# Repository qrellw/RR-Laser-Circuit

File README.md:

# Tài liệu Kỹ thuật Dự án: Thiết bị Đo nhịp thở (RR-Laser-Circuit)

Tài liệu này cung cấp các thông số kỹ thuật, nguyên lý hoạt động và hướng dẫn cấu hình phần mềm cho hệ thống thiết bị đo nhịp thở ứng dụng cảm biến quang học.

## 1. Tổng quan Nguyên lý Hoạt động
Hệ thống đo nhịp thở dựa trên phương pháp đo chuyển vị quang học (Optical Displacement Sensing):
*   **Khối Phát:** Module Laser bán dẫn (bước sóng 650nm) chiếu tia sáng vào một gương phản xạ gắn trên lồng ngực.
*   **Khối Thu:** Hai photodiode (BPW34) được bố trí thành dạng bi-cell. Sự dịch chuyển của gương theo nhịp thở làm thay đổi vị trí tia phản xạ trên bề mặt bi-cell, dẫn đến sự thay đổi tương quan dòng quang điện giữa hai kênh.
*   **Khối Xử lý Tín hiệu (Analog):** Sử dụng duy nhất 1 Op-amp **MCP6004** (4 kênh). Hai kênh được cấu hình làm mạch Transimpedance Amplifier (TIA) để chuyển đổi dòng quang điện (µA) thành điện áp (Va, Vb). Hai kênh còn lại làm mạch Buffer để ổn định trở kháng trước khi đưa vào ADC.
*   **Khối Số hóa (Digital):** Vi điều khiển ESP32-C3 thu thập dữ liệu từ ADC (ADS1115) qua giao tiếp I2C, xử lý thuật toán và truyền dữ liệu qua giao thức Bluetooth Low Energy (BLE).

## 2. Sơ đồ Chân Vi điều khiển (Pinout)
*Thiết bị sử dụng module ESP32-C3 SuperMini.*

| Chức năng | Chân GPIO | Trạng thái Logic | Ghi chú |
| :--- | :--- | :--- | :--- |
| **I2C SDA** | GPIO8 | Bidirectional | Giao tiếp dữ liệu với ADS1115 |
| **I2C SCL** | GPIO9 | Output | Xung nhịp I2C cho ADS1115 |
| **LASER_EN** | GPIO4 | Output | HIGH: Bật công tắc MOSFET cấp dòng cho Laser (3.3V) |
| **VBAT_SENSE** | GPIO0 | Analog Input | Đọc điện áp Pin qua cầu phân áp 100k/100k (ADC1) |

*(Lưu ý: Thiết kế V1 đã loại bỏ hoàn toàn mạch Boost 5V. Laser được cấp trực tiếp nguồn 3.3V từ LDO. Chân `BOOST_EN` cũ đã bị xóa khỏi phần mềm).*

## 3. Cấu hình ADC (ADS1115) và Quy trình Lấy mẫu
*   **Địa chỉ I2C:** `0x48` (Chân ADDR nối GND).
*   **Độ phân giải:** 16-bit.
*   **Phân bổ Kênh (Multiplexer):**
    *   `AIN0` = Điện áp **Va** (Tín hiệu TIA kênh 1).
    *   `AIN1` = Điện áp **Vb** (Tín hiệu TIA kênh 2).
    *   `AIN2` = Điện áp **Vbias** (Mức nền tham chiếu thực tế, thường ~0.23V).

**Quy trình lấy mẫu (Sampling Sequence):**
Để triệt tiêu nhiễu môi trường và ánh sáng phòng, phần mềm cần thực hiện chu kỳ lấy mẫu theo trình tự nghiêm ngặt sau:
1.  Đặt `LASER_EN` = HIGH (Laser phát sáng).
2.  Trễ (Delay) **50ms** để mạch lọc RC (fc ≈ 15Hz) xác lập giá trị.
3.  Đọc giá trị ADC tại `AIN0`, `AIN1` và `AIN2` (Lưu vào biến `Va_on`, `Vb_on`, `Vbias`).
4.  Đặt `LASER_EN` = LOW (Tắt Laser).
5.  Trễ **50ms**.
6.  Đọc giá trị ADC tại `AIN0`, `AIN1` (Lưu vào biến `Va_off`, `Vb_off`).

## 4. Công thức Tính toán Tín hiệu
Mức nền thực tế (Vbias) được đọc từ `AIN2` giúp bù trừ sai số do nhiệt độ và dung sai linh kiện. Phần mềm cần thực hiện các bước tính toán sau:

1.  **Trích xuất dòng quang điện (tỉ lệ với điện áp):**
    *   `Ia = Va_on - Va_off`
    *   `Ib = Vb_on - Vb_off`
    *(Việc trừ mẫu sáng cho mẫu tối giúp triệt tiêu hoàn toàn mức nền Vbias và ánh sáng môi trường).*

2.  **Tính tỉ số vị trí (Position Ratio - r):**
    \[
 r = \frac{I_a - k \cdot I_b}{I_a + k \cdot I_b} 
\]
    *Trong đó:* `k` là hệ số bù sai lệch giữa hai kênh (được xác định thực nghiệm). Giá trị `r` dao động từ -1 đến 1, phản ánh chính xác vị trí dịch chuyển của tia Laser.

## 5. Quản lý Năng lượng và Cảnh báo Phần cứng
*   **Nguồn cấp:** Pin Lithium-Ion 3.7V (có mạch bảo vệ PCM, dung lượng 800mAh).
*   **Sạc:** IC TP4056 (giới hạn dòng sạc ~300mA qua trở PROG).
*   **Nguồn Analog:** LDO MCP1700-3302 (siêu sạch, cấp cho MCP6004 và ADS1115).
*   **Nguồn Digital:** LDO AP2112K-3.3 (cấp cho ESP32-C3).
*   **Đo Pin:** Điện áp Pin được chia áp 1:2 qua cầu trở 100kΩ trước khi vào GPIO0. Công thức quy đổi: `V_pin = ADC_Value * 2`. Cảnh báo pin yếu nên được thiết lập ở ngưỡng **3.5V**.
*   **Cảnh báo Phần cứng:** Cổng USB trên module ESP32-C3 chỉ dùng để nạp firmware (đã ngắt kết nối nguồn 5V từ USB vào LDO nội bộ để tránh xung đột). Do đó, **không thực hiện đo nhịp thở trong quá trình đang sạc pin**.

## 6. Ghi chú Phát triển Firmware (Software)
*   **Thư viện đề xuất:** `Adafruit_ADS1X15` (đọc ADC), `NimBLE-Arduino` (giao tiếp BLE).
*   **Xử lý tín hiệu số (DSP):** Tín hiệu `r` thô chứa nhiễu tần số thấp và các dao động chậm. Cần áp dụng bộ lọc thông dải (Bandpass Filter):
    *   Dải tần nhịp thở (RR): **0.1 Hz đến 0.4 Hz** (tương đương 6 - 24 nhịp/phút).
    *   Khuyến nghị sử dụng thuật toán lọc trung bình trượt (Moving Average) hoặc bộ lọc IIR (Butterworth).
*   **Chu kỳ lấy mẫu:** Tần số lấy mẫu khuyến nghị từ **10Hz - 20Hz** để đảm bảo độ phân giải cho tín hiệu nhịp thở mà không gây quá tải bộ nhớ.

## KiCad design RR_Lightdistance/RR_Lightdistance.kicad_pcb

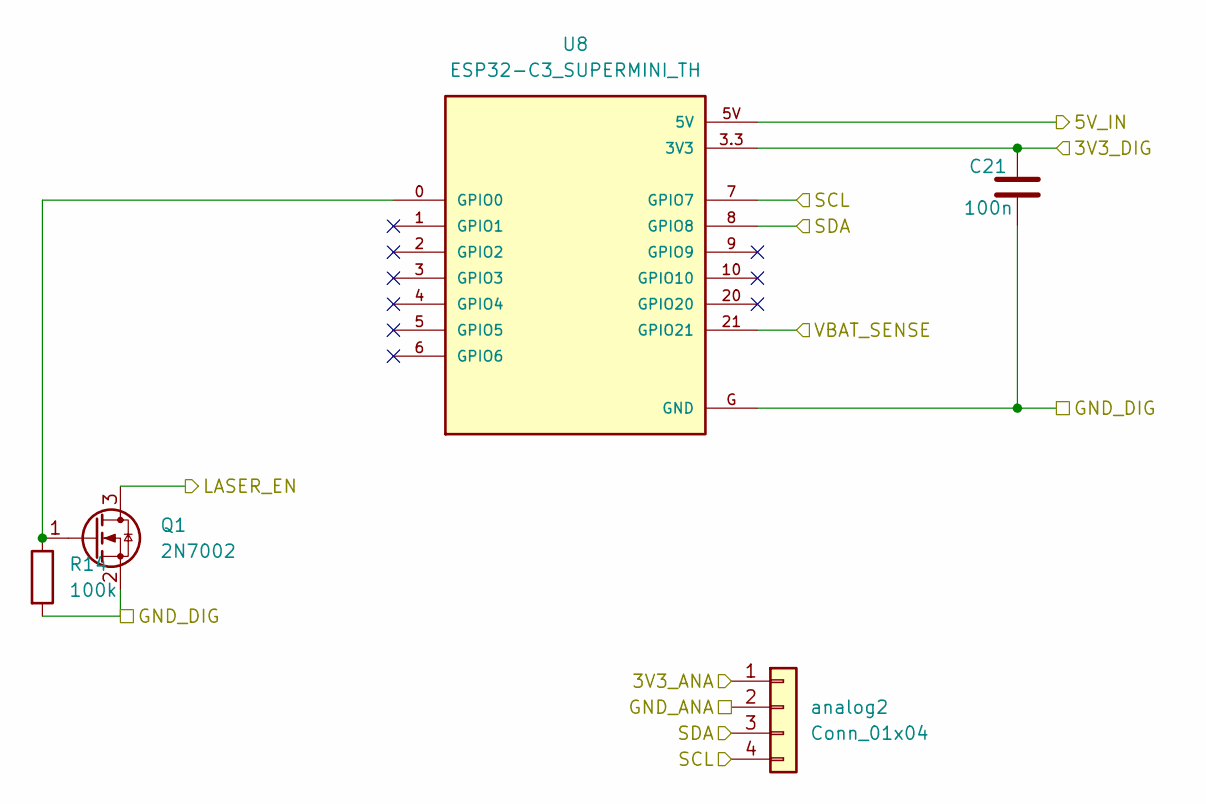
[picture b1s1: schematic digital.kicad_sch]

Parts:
C21: 100n; C_0603_1608Metric
Q1: 2N7002; SOT-23
R14: 100k; R_0603_1608Metric
U8: ESP32-C3_SUPERMINI_TH; MODULE_ESP32-C3_SUPERMINI_TH
analog2: Conn_01x04; JST_SH_BM04B-SRSS-TB_1x04-1MP_P1.00mm_Vertical

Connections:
/Analog/3V3_ANA: analog2.1; also elsewhere on the board
/Analog/GND_ANA: analog2.2; also elsewhere on the board
/Analog/SCL: U8.7 (GPIO7), analog2.4; also elsewhere on the board
/Analog/SDA: U8.8 (GPIO8), analog2.3; also elsewhere on the board
/Digital/3V3_DIG: C21.1, U8.3.3 (3V3); also elsewhere on the board
/Digital/5V_IN: U8.5V; also elsewhere on the board
/Digital/GND_DIG: C21.2, Q1.2 (S), R14.2, U8.G (GND); also elsewhere on the board
/Digital/LASER_EN: Q1.3 (D); also elsewhere on the board
/Digital/VBAT_SENSE: U8.21 (GPIO21); also elsewhere on the board
unnamed: Q1.1 (G), R14.1, U8.0 (GPIO0)

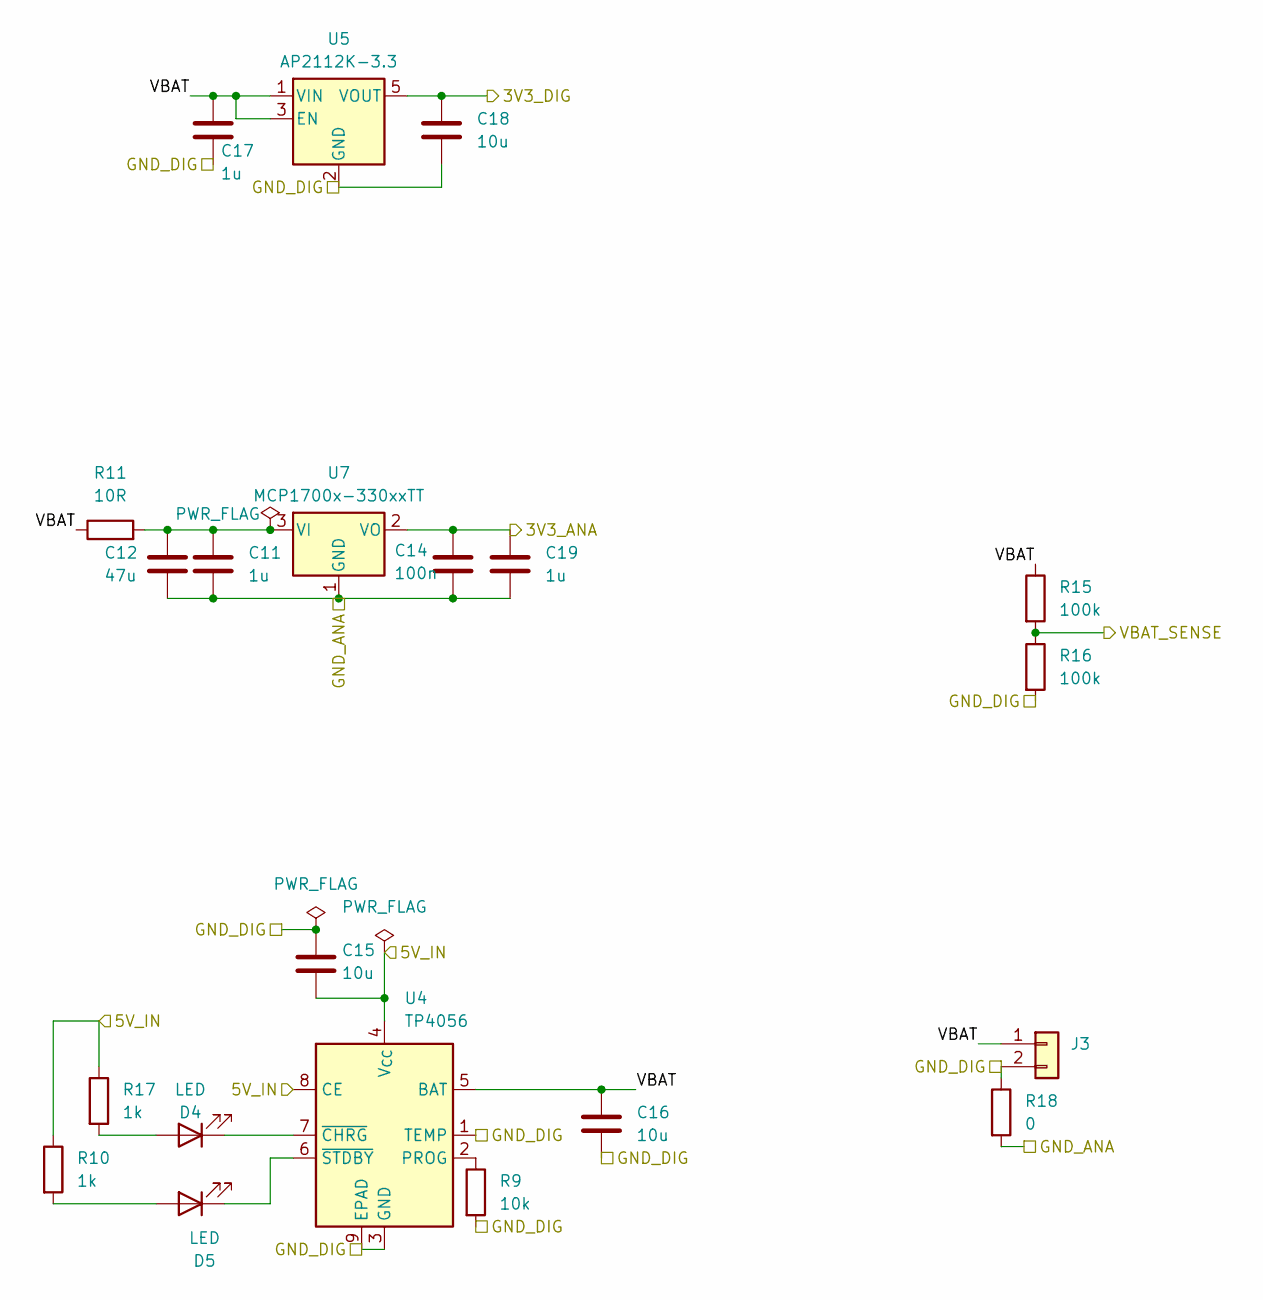
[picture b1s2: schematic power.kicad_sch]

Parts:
C11, C17, C19: 1u; C_0603_1608Metric
C12: 47u; C_0805_2012Metric
C14: 100n; C_0603_1608Metric
C15, C16, C18: 10u; C_0805_2012Metric
D4, D5: LED; LED_0805_2012Metric
J3: JST_SH_BM02B-SRSS-TB_1x02-1MP_P1.00mm_Vertical
R9: 10k; R_0603_1608Metric
R10, R17: 1k; R_0603_1608Metric
R11: 10R; R_0603_1608Metric
R15, R16: 100k; R_0603_1608Metric
R18: 0; R_0805_2012Metric
U4: TP4056; SOIC-8-1EP_3.9x4.9mm_P1.27mm_EP2.41x3.3mm_ThermalVias
U5: AP2112K-3.3; SOT-23-5
U7: MCP1700x-330xxTT; SOT-23

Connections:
/Analog/3V3_ANA: C14.1, C19.1, U7.2 (VO); also elsewhere on the board
/Analog/GND_ANA: C11.2, C12.2, C14.2, C19.2, R18.2, U7.1 (GND); also elsewhere on the board
/Digital/3V3_DIG: C18.1, U5.5 (VOUT); also elsewhere on the board
/Digital/5V_IN: C15.2, R10.1, R17.1, U4.4 (V_{CC}), U4.8 (CE); also elsewhere on the board
/Digital/GND_DIG: C15.1, C16.2, C17.2, C18.2, J3.2, R9.2, R16.2, R18.1, U4.1 (TEMP), U4.3 (GND), U4.9 (EPAD), U5.2 (GND); also elsewhere on the board
/Digital/VBAT_SENSE: R15.2, R16.1; also elsewhere on the board
/Power/VBAT: C16.1, C17.1, J3.1, R11.1, R15.1, U4.5 (BAT), U5.1 (VIN), U5.3 (EN)
unnamed: D4.2 (A), R17.2
unnamed: D4.1 (K), U4.7 (~CHRG)
unnamed: D5.2 (A), R10.2
unnamed: D5.1 (K), U4.6 (~STDBY)
unnamed: R9.1, U4.2 (PROG)
unnamed: C11.1, C12.1, R11.2, U7.3 (VI)

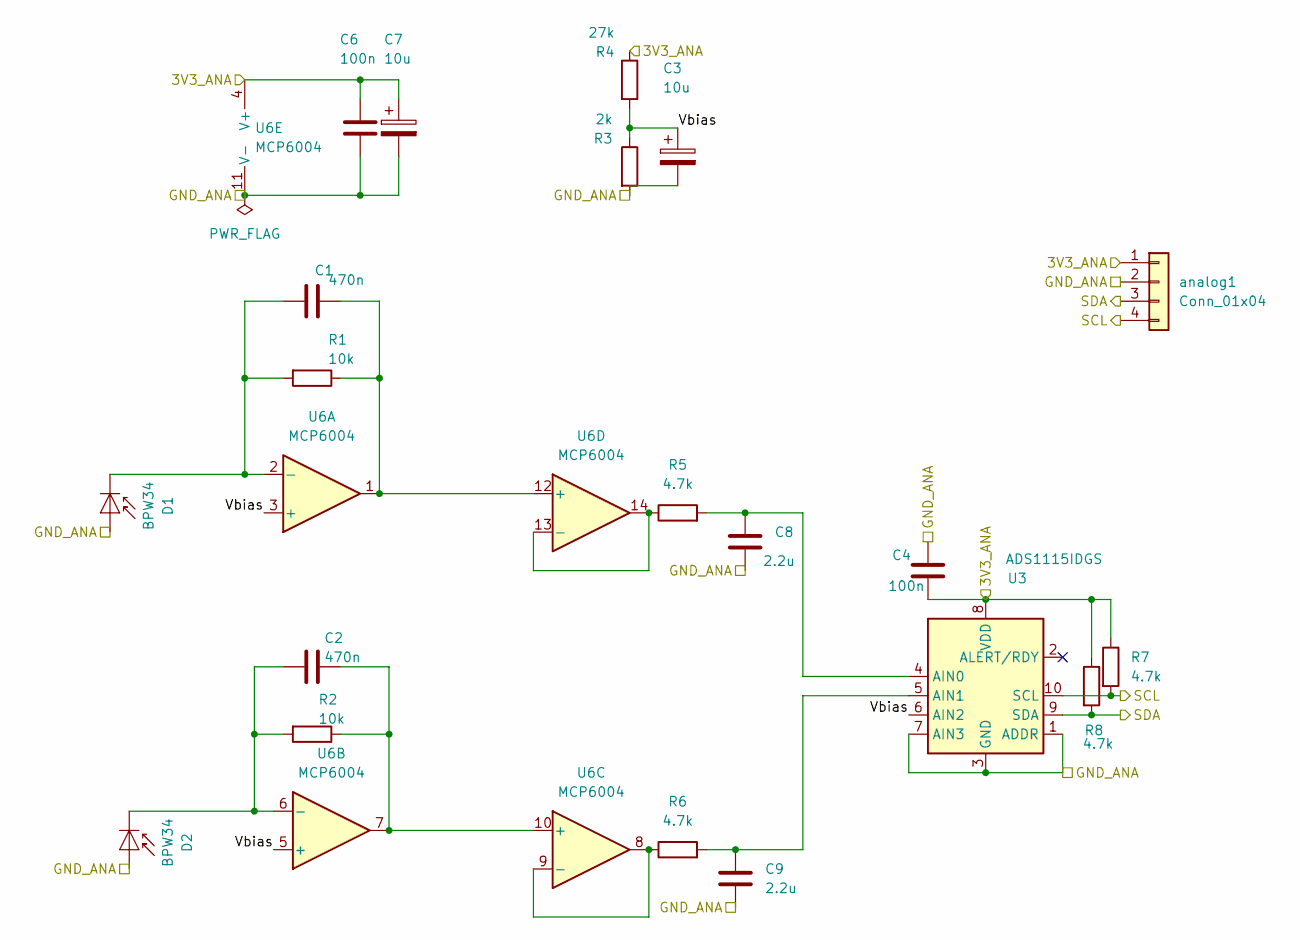
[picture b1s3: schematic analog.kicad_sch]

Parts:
C1, C2: 470n; C_0603_1608Metric
C3, C7: 10u; C_0805_2012Metric
C4, C6: 100n; C_0603_1608Metric
C8, C9: 2.2u; C_0603_1608Metric
D1, D2: BPW34; Osram_BPW34S-SMD
R1, R2: 10k; R_0603_1608Metric
R3: 2k; R_0603_1608Metric
R4: 27k; R_0603_1608Metric
R5, R6, R7, R8: 4.7k; R_0603_1608Metric
U3: ADS1115IDGS; TSSOP-10_3x3mm_P0.5mm
U6: MCP6004; SOIC-14_3.9x8.7mm_P1.27mm
analog1: Conn_01x04; JST_SH_BM04B-SRSS-TB_1x04-1MP_P1.00mm_Vertical

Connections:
/Analog/3V3_ANA: C4.2, C6.1, C7.1, R4.1, R7.1, R8.1, U3.8 (VDD), U6.4 (V+), analog1.1; also elsewhere on the board
/Analog/GND_ANA: C3.2, C4.1, C6.2, C7.2, C8.2, C9.2, D1.2 (A), D2.2 (A), R3.2, U3.1 (ADDR), U3.3 (GND), U3.7 (AIN3), U6.11 (V-), analog1.2; also elsewhere on the board
/Analog/SCL: R7.2, U3.10 (SCL), analog1.4; also elsewhere on the board
/Analog/SDA: R8.2, U3.9 (SDA), analog1.3; also elsewhere on the board
/Analog/Vbias: C3.1, R3.1, R4.2, U3.6 (AIN2), U6.3 (+), U6.5 (+)
unnamed: C1.2, D1.1 (K), R1.2, U6.2 (-)
unnamed: C2.2, D2.1 (K), R2.2, U6.6 (-)
unnamed: C8.1, R5.2, U3.4 (AIN0)
unnamed: C9.1, R6.2, U3.5 (AIN1)
unnamed: C2.1, R2.1, U6.7, U6.10 (+)
unnamed: R6.1, U6.8, U6.9 (-)
unnamed: C1.1, R1.1, U6.1, U6.12 (+)
unnamed: R5.1, U6.13 (-), U6.14

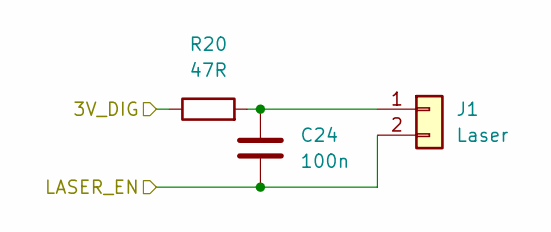
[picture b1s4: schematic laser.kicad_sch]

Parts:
C24: 100n; C_0603_1608Metric
J1: Laser; JST_SH_BM02B-SRSS-TB_1x02-1MP_P1.00mm_Vertical
R20: 47R; R_0603_1608Metric

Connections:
/Digital/3V3_DIG: R20.1; also elsewhere on the board
/Digital/LASER_EN: C24.2, J1.2; also elsewhere on the board
unnamed: C24.1, J1.1, R20.2

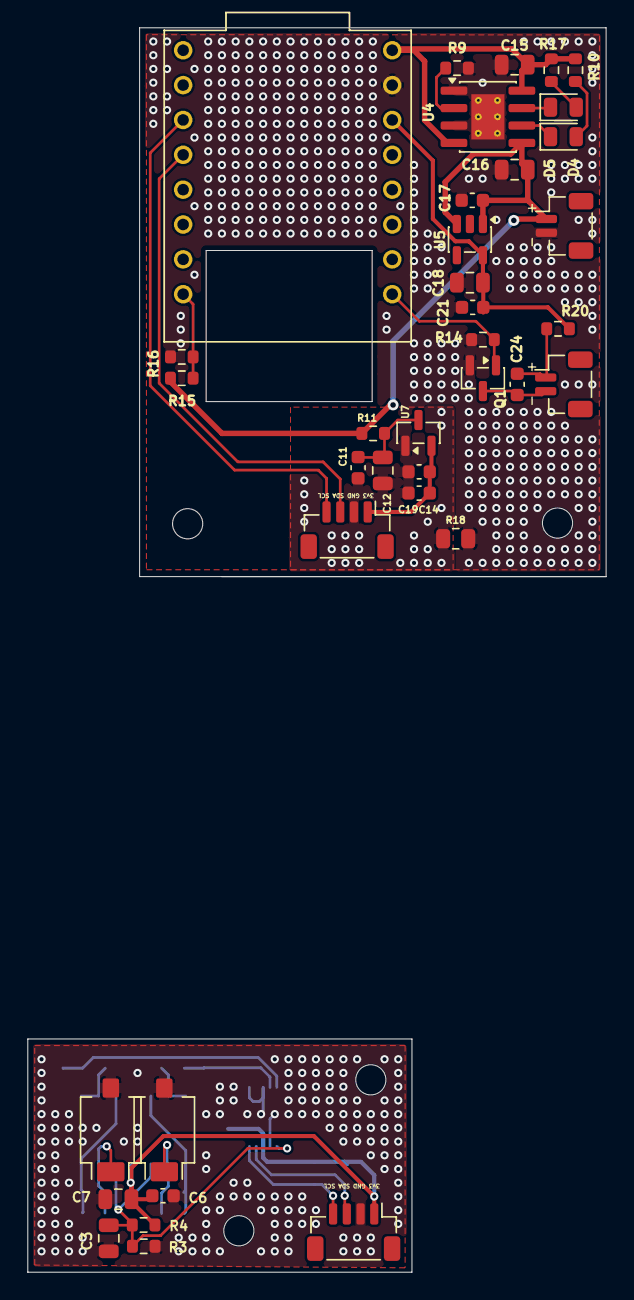
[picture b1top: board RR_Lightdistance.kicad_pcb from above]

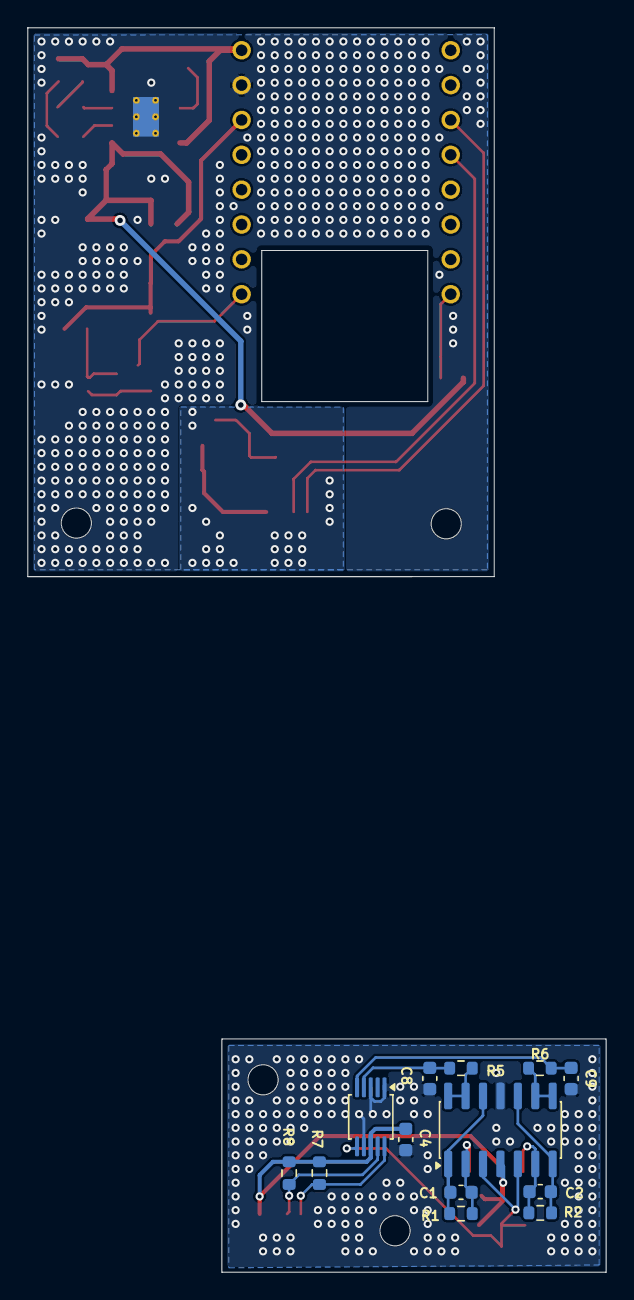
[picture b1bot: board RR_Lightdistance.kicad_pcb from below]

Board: 2 copper layers, 42.1 x 90.7 mm, 54 parts (13 on the bottom side), 27 nets.

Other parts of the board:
H1, H2, H3, H4: MountingHole_2.2mm_M2

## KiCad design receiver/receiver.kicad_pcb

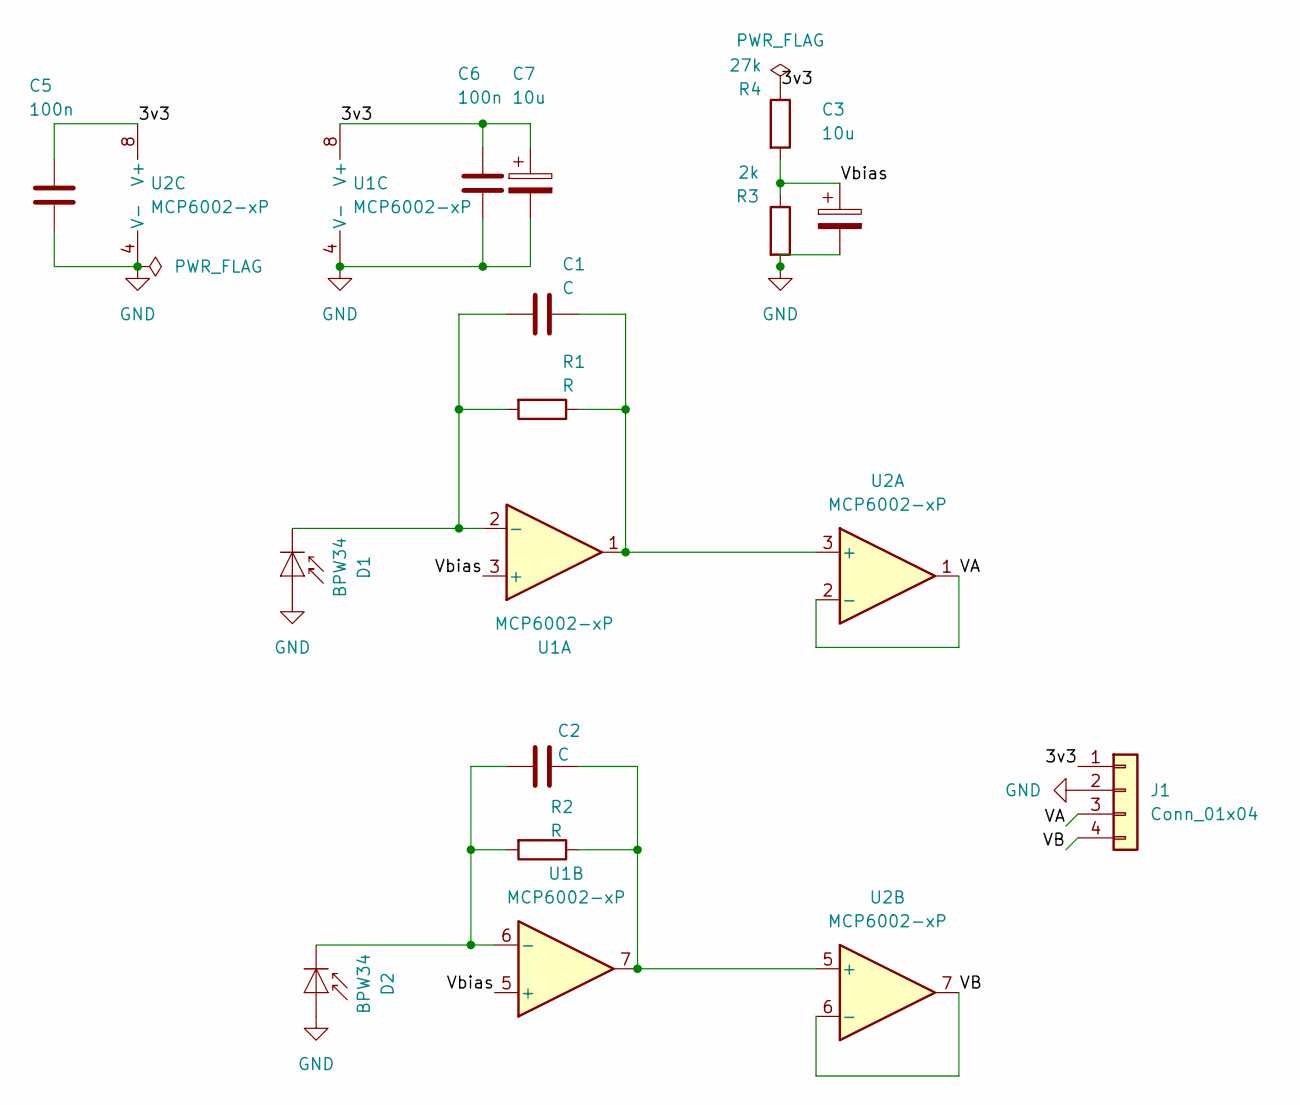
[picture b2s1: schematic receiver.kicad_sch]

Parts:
C1, C2: C; C_Disc_D5.0mm_W2.5mm_P5.00mm
C3, C7: 10u; CP_Radial_D5.0mm_P2.50mm
C5, C6: 100n; C_Disc_D5.0mm_W2.5mm_P5.00mm
D1, D2: BPW34; Osram_DIL2_4.3x4.65mm_P5.08mm
J1: Conn_01x04; PinHeader_1x04_P2.54mm_Vertical
R1, R2: R; R_Axial_DIN0207_L6.3mm_D2.5mm_P2.54mm_Vertical
R3: 2k; R_Axial_DIN0207_L6.3mm_D2.5mm_P10.16mm_Horizontal
R4: 27k; R_Axial_DIN0207_L6.3mm_D2.5mm_P10.16mm_Horizontal
U1, U2: MCP6002-xP; DIP-8_W7.62mm

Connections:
/3v3: C5.1, C6.1, C7.1, J1.1, R4.1, U1.8 (V+), U2.8 (V+)
/VA: J1.3, U2.1, U2.2 (-)
/VB: J1.4, U2.6 (-), U2.7
/Vbias: C3.1, R3.1, R4.2, U1.3 (+), U1.5 (+)
GND: C3.2, C5.2, C6.2, C7.2, D1.2 (A), D2.2 (A), J1.2, R3.2, U1.4 (V-), U2.4 (V-)
unnamed: C1.2, D1.1 (K), R1.2, U1.2 (-)
unnamed: C2.2, D2.1 (K), R2.2, U1.6 (-)
unnamed: C1.1, R1.1, U1.1, U2.3 (+)
unnamed: C2.1, R2.1, U1.7, U2.5 (+)

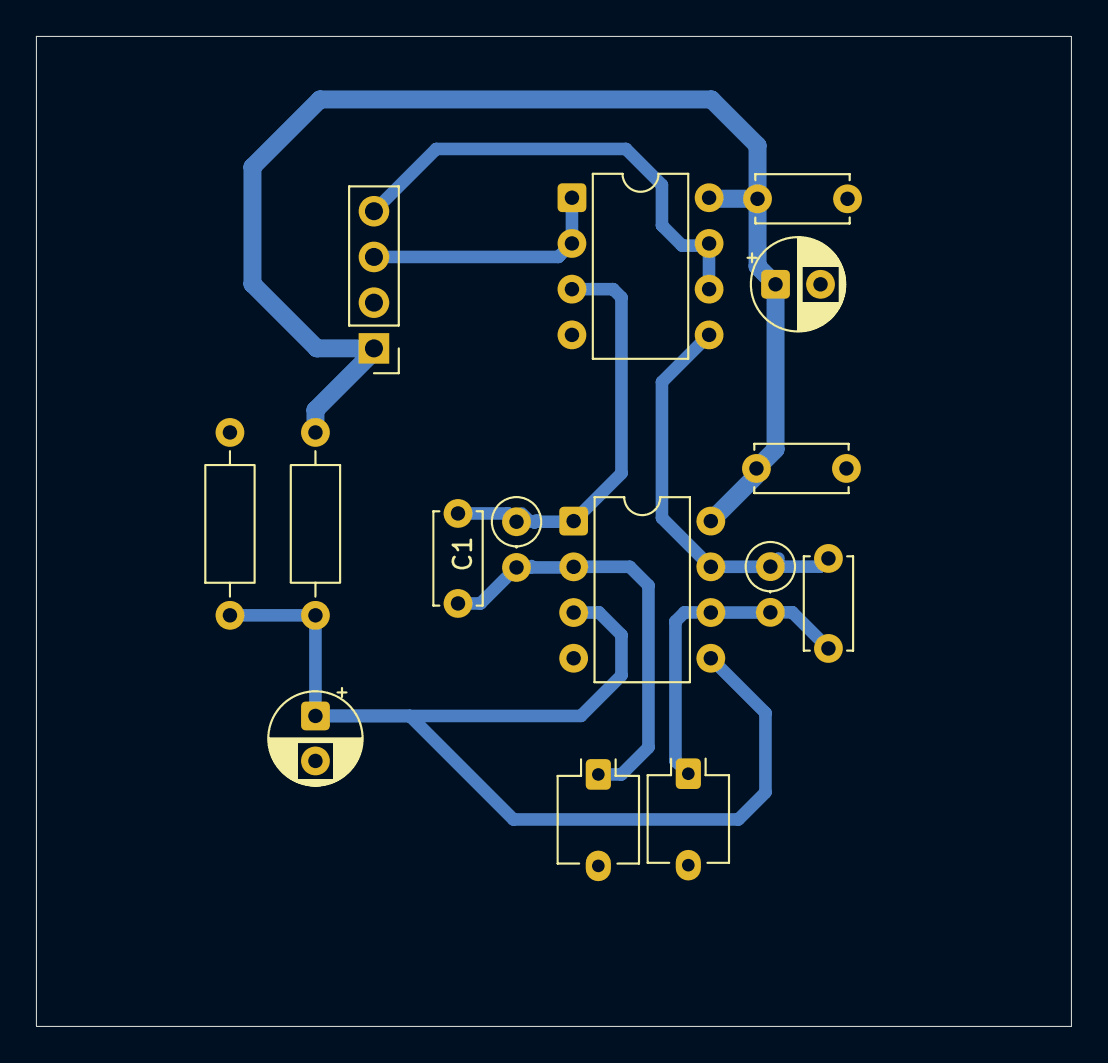
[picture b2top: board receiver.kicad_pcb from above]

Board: 2 copper layers, 57.5 x 55.0 mm, 15 parts (0 on the bottom side), 9 nets.
